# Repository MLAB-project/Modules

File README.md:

# MLAB hardware modules main repository

The MLAB Project was created to develop an universal kit to support hobbyist and professionals in the construction of simple or more complicated devices and instruments (robots, automation systems, testing kits and so on). It is primarily intended for engineers and scientists and it is in continuous development since 2003.

**This repository is archived because its contents have been split into separate repositories in the [MLAB-modules](https://github.com/mlab-modules/) organization. The development of new [MLAB](https://www.mlab.cz) components is still in progress and development has not been suspended. You can read about the reasons of the repository split on the [Discussions thread](https://github.com/orgs/MLAB-project/discussions/1).**

This repository is only a component of the [complete MLAB system](http://www.mlab.cz/)

## Modules

The principle of [Modular LABoratory](http://www.mlab.cz) is based on decomposition of complex systems into smaller cells or bricks (in MLAB called [modules](http://wiki.mlab.cz/doku.php?id=en:moduly)) such as communication interfaces, operational amplifiers, CPU modules, FPGA programmers and many other. Over years of development, [tenths of modules have been created](https://github.com/mlab-modules) - for easier orientation they are sorted into categories which are the first-level folders of this repository. Many modules are included as [repository submodules](https://git-scm.com/book/en/v2/Git-Tools-Submodules) in this parent repository. 

When creating modules, great emphasis is put on the quality of design and construction. The results can, therefore, meet the standards of even the most demanding users from the community of researchers, experimenters and innovators.

## How to start using MLAB

Further information can be found on [MLAB Wiki](http://wiki.mlab.cz/).

There is also a [Mailing list](https://groups.google.com/forum/#!forum/mlab-users) available for users and developers.

## Compatibility

Thanks to careful design, most of the modules are dimensionally and electrically compatible with many other products. Examples include the Arduino platform, the Merkur construction set, optical tables and DIN switchboard systems.

## Applications

See the [list of designs](http://home.mlab.cz/Server/GenIndex/GenIndex.php?path=%2FDesigns&lang=en) for an illustration of the wide spectrum of possible applications.

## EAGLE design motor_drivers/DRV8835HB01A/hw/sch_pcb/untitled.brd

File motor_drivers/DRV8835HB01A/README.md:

[Czech](./README.cs.md)
<!--- module --->
# DRV8835HB01A
<!--- Emodule --->

<!--- subtitle --->2x H-bridge 2V - 11V<!--- Esubtitle --->

<!--- description --->H-bridge-based ICs DRV8835HB. Allows you to control two DC motors in the range voltage 2V to 11V and maximum current of 1.5 A on the engine, or parallel, where it is then possible to control the 3A engine. Or the module can be used to control a stepper motor. <!--- Edescription --->

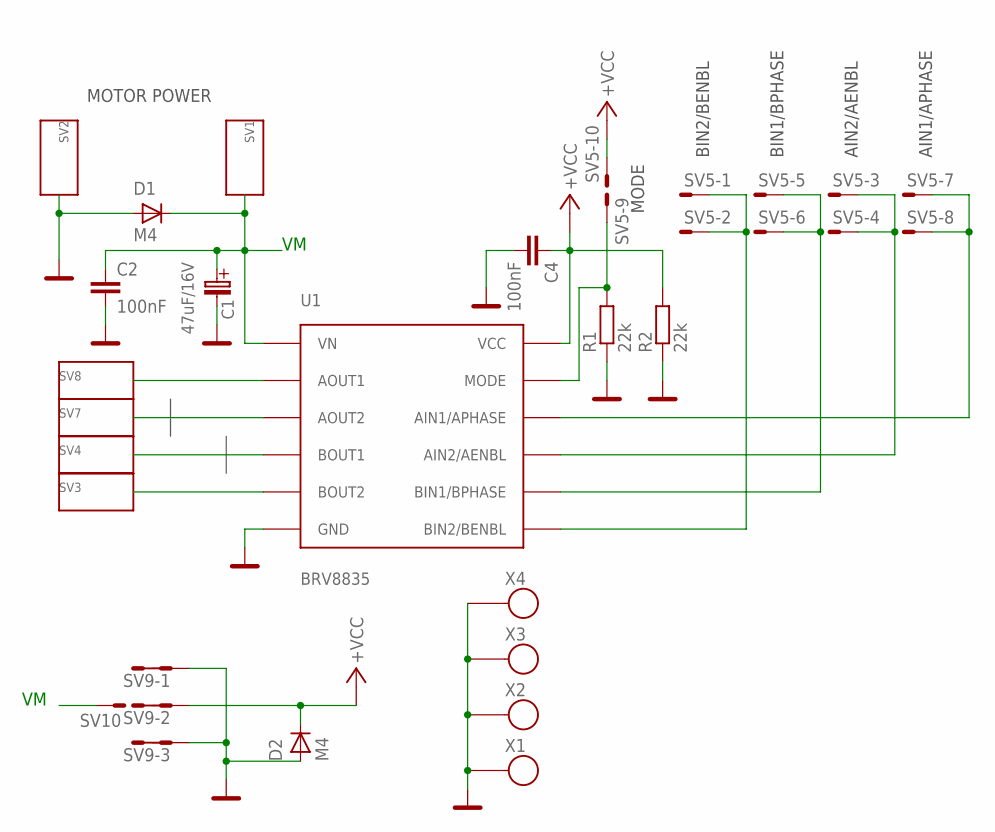
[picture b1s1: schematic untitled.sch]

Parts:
C1: 47uF/16V; C
C2, C4: 100nF; C0805
D1, D2: M4; SMA
R1, R2: 22k; 0805
SV1, SV2, SV3, SV4, SV7, SV8: WAGO256
SV5: MA05-3; MA05-2
SV9: MA03-2
SV10: MA01-1
U1: BRV8835; WSON
X1, X2, X3, X4: SROUB3M

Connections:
+VCC: C4.1, D2.K (C), R2.2, SV5.10, SV9.3, SV9.4, U1.12 (VCC)
GND: C1.- (C_EL-), C2.2, C4.2, D1.A, D2.A, R1.1, R2.1, SV2.1, SV2.A1, SV9.1, SV9.2, SV9.5, SV9.6, U1.6 (GND), U1.P1 (GND), U1.P2 (GND), U1.P3 (GND), U1.P4 (GND), U1.P5 (GND), U1.P6 (GND), U1.P7 (GND), U1.P8 (GND), X1.P$1, X2.P$1, X3.P$1, X4.P$1
unnamed: SV3.1, SV3.A1, U1.5 (BOUT2)
unnamed: SV5.5, SV5.6, U1.8 (BIN1/BPHASE)
unnamed: SV4.1, SV4.A1, U1.4 (BOUT1)
unnamed: SV7.1, SV7.A1, U1.3 (AOUT2)
unnamed: SV8.1, SV8.A1, U1.2 (AOUT1)
unnamed: SV5.1, SV5.2, U1.7 (BIN2/BENBL)
unnamed: R1.2, SV5.9, U1.11 (MODE)
unnamed: SV5.3, SV5.4, U1.9 (AIN2/AENBL)
unnamed: SV5.7, SV5.8, U1.10 (AIN1/APHASE)
VN: C1.+ (C_EL+), C2.1, D1.K (C), SV1.1, SV1.A1, SV10.1, U1.1 (VN)

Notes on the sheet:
AIN1/APHASE
AIN2/AENBL
BIN1/BPHASE
BIN2/BENBL
MODE
MOTOR POWER

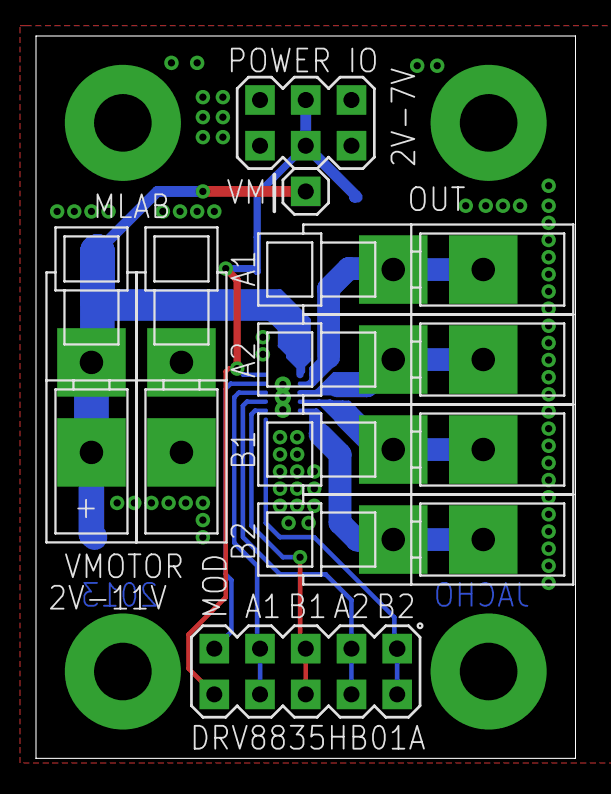
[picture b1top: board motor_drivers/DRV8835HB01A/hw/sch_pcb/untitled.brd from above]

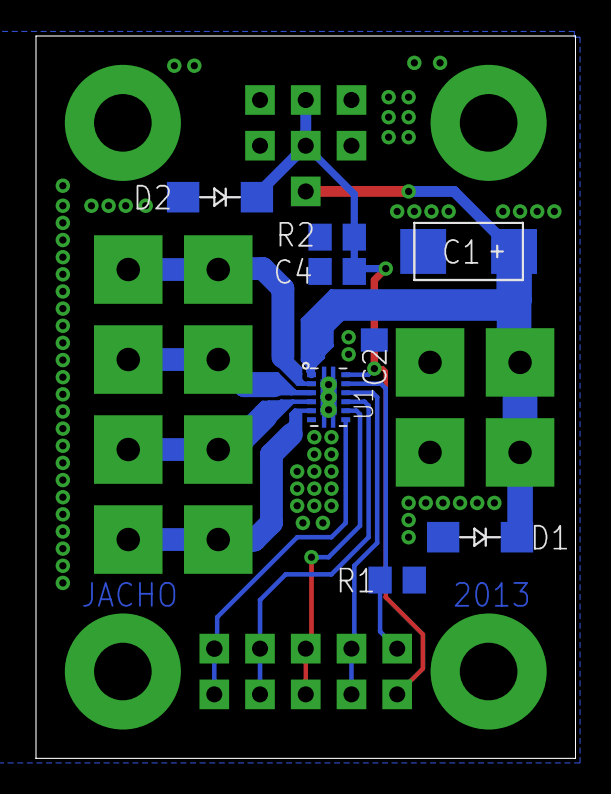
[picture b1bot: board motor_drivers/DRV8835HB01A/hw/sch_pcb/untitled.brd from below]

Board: 2 copper layers, 30.0 x 40.1 mm, 21 parts (8 on the bottom side), 12 nets.

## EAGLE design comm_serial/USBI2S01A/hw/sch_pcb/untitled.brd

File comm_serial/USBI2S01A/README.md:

[Czech](./README.cs.md)
<!--- module --->
# USBI2S01A
<!--- Emodule --->

<!--- subtitle --->USB to I2S bridge<!--- Esubtitle --->

<!--- description --->USB to I2S converter for interfacin I2S audio devices to standard USB port. It is compatible with UAC standard.<!--- Edescription --->

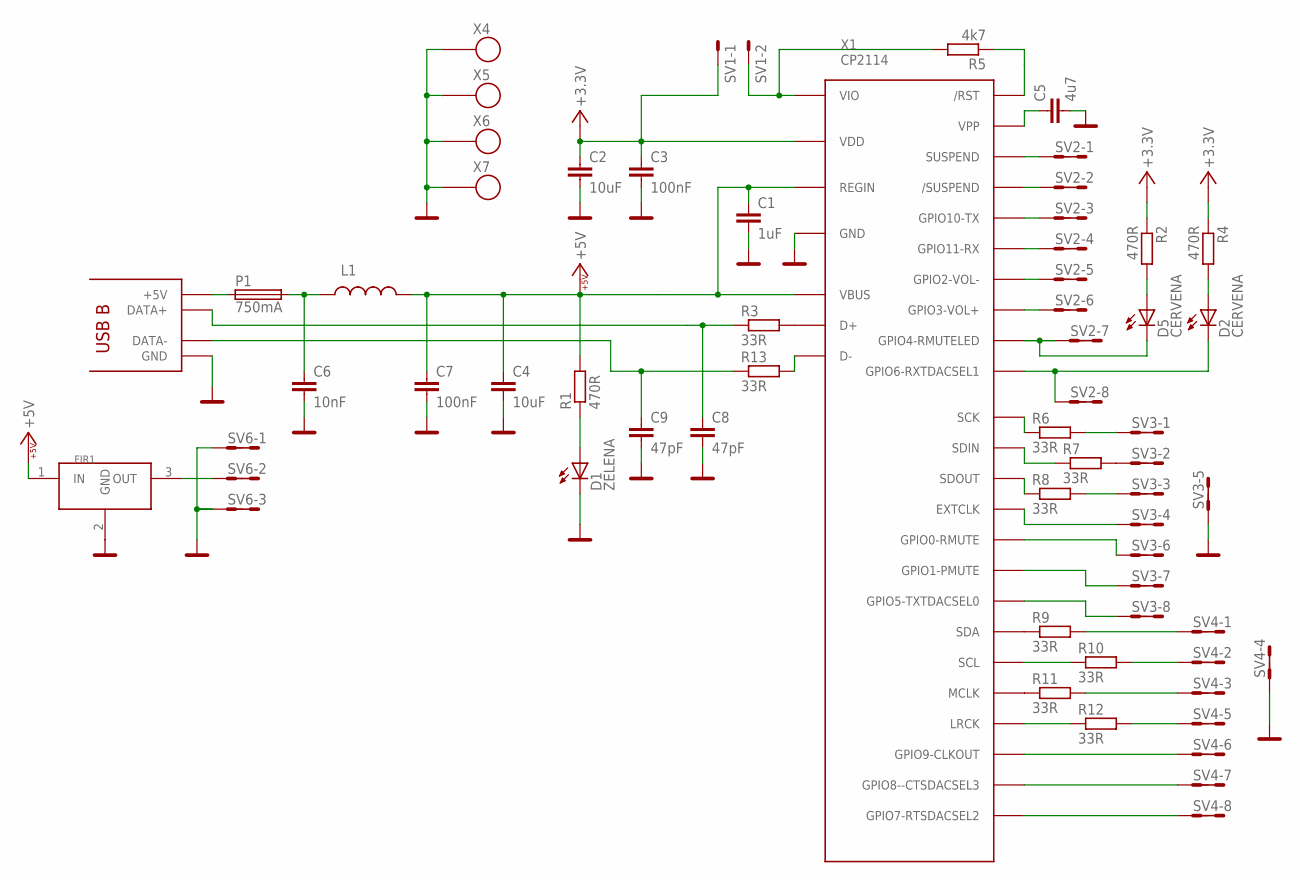
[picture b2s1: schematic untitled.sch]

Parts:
C1: 1uF; C0805
C2, C4: 10uF; C0805
C3, C7: 100nF; C0805
C5: 4u7; C0805
C6: 10nF; C0805
C8, C9: 47pF; C0805
D1: ZELENA; 1206_2
D2, D5: CERVENA; 1206_2
FIR1: FILTR0805; F0805
L1: L0805
P1: 750mA; 1812
R1, R2, R4: 470R; 0805
R3, R6, R7, R8, R9, R10, R11, R12, R13: 33R; 0805
R5: 4k7; 0805
SV1: MA02-1
SV2, SV3, SV4: MA08-2
SV6: MA03-2
X1: CP2114; QFN-32
X3: USB_B
X4, X5, X6, X7: SROUB3M

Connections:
+3.3V: C2.1, C3.1, R2.1, R4.1, SV1.1, X1.7 (VDD)
+5V: C1.1, C4.1, C7.1, FIR1.1 (IN), L1.2, R1.2, X1.8 (REGIN), X1.9 (VBUS)
/SUSPEND: SV2.3, SV2.4, X1.17 (/SUSPEND)
EXTCLK: SV3.7, SV3.8, X1.31 (EXTCLK)
GND: C1.2, C2.2, C3.2, C4.2, C5.2, C6.2, C7.2, C8.2, C9.2, D1.K (C), FIR1.2 (GND), SV3.9, SV3.10, SV4.7, SV4.8, SV6.1, SV6.2, SV6.5, SV6.6, X1.3 (GND), X1.EXP (GND), X3.4 (GND), X3.GND, X3.GND2 (GND), X4.P$1, X5.P$1, X6.P$1, X7.P$1
GP0: SV3.11, SV3.12, X1.30 (GPIO0-RMUTE)
GP1: SV3.13, SV3.14, X1.29 (GPIO1-PMUTE)
GP2: SV2.9, SV2.10, X1.14 (GPIO2-VOL-)
GP3: SV2.11, SV2.12, X1.13 (GPIO3-VOL+)
GP4: D5.K (C), SV2.13, SV2.14, X1.12 (GPIO4-RMUTELED)
GP5: SV3.15, SV3.16, X1.28 (GPIO5-TXTDACSEL0)
GP6: D2.K (C), SV2.15, SV2.16, X1.11 (GPIO6-RXTDACSEL1)
GP7: SV4.15, SV4.16, X1.19 (GPIO7-RTSDACSEL2)
GP08: SV4.13, SV4.14, X1.20 (GPIO8--CTSDACSEL3)
GP9: SV4.11, SV4.12, X1.22 (GPIO9-CLKOUT)
GP10: SV2.5, SV2.6, X1.16 (GPIO10-TX)
GP11: SV2.7, SV2.8, X1.15 (GPIO11-RX)
LRCK: R12.2, SV4.9, SV4.10
MCLK: R11.2, SV4.5, SV4.6
unnamed: C8.1, R3.1, X3.3 (DATA+)
unnamed: C9.1, R13.1, X3.2 (DATA-)
unnamed: FIR1.3 (OUT), SV6.3, SV6.4
unnamed: C5.1, X1.21 (VPP)
unnamed: P1.1, X3.1 (+5V)
unnamed: D1.A, R1.1
unnamed: C6.1, L1.1, P1.2
unnamed: R3.2, X1.4 (D+)
unnamed: R13.2, X1.5 (D-)
unnamed: D5.A, R2.2
unnamed: D2.A, R4.2
unnamed: R5.1, X1.10 (/RST)
unnamed: R8.1, X1.32 (SDOUT)
unnamed: R7.1, X1.1 (SDIN)
unnamed: R6.1, X1.2 (SCK)
unnamed: R9.1, X1.27 (SDA)
unnamed: R10.1, X1.26 (SCL)
unnamed: R11.1, X1.25 (MCLK)
unnamed: R12.1, X1.23 (LRCK)
SCK: R6.2, SV3.1, SV3.2
SCL: R10.2, SV4.3, SV4.4
SDA: R9.2, SV4.1, SV4.2
SDIN: R7.2, SV3.3, SV3.4
SDOUT: R8.2, SV3.5, SV3.6
SUSPEND: SV2.1, SV2.2, X1.18 (SUSPEND)
VIO: R5.2, SV1.2, X1.6 (VIO)

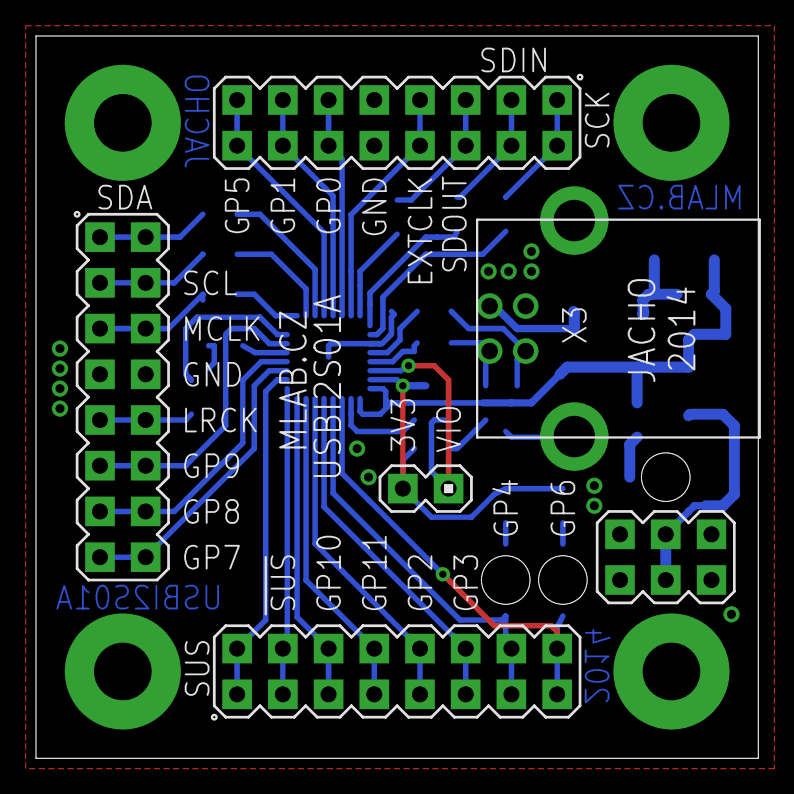
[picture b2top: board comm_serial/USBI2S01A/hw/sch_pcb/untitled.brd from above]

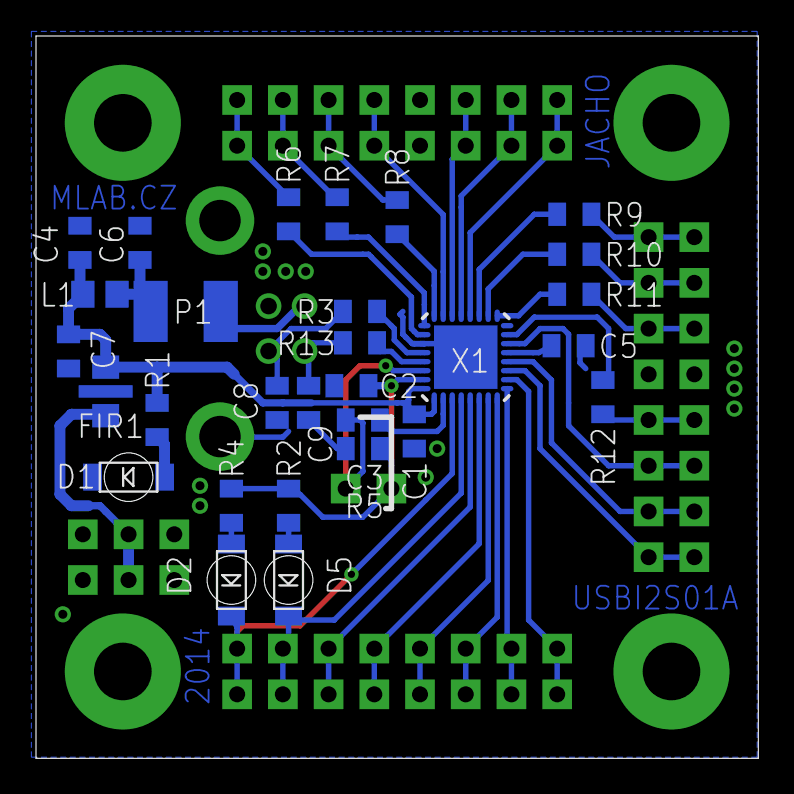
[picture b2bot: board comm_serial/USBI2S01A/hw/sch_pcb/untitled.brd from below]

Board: 2 copper layers, 40.1 x 40.1 mm, 39 parts (29 on the bottom side), 45 nets.

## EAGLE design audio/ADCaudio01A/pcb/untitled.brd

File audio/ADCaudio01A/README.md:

<!--- PrjInfo ---> <!--- Please remove this line after manually editing --->
<!--- 00a56be08b96043df9e37d6aff7b6990 --->
<!--- Created:2022-02-16 22:09:44.047760: ---> 
<!--- Author:: ---> 
<!--- AuthorEmail:: ---> 
<!--- Tags:: ---> 
<!--- Ust:: ---> 
<!--- Label --->
<!--- ELabel ---> 
<!--- Name:ADCaudio01A: --->
# ADCaudio01A
<!--- LongName --->
## Audio to digital converter
<!--- ELongName ---> 

<!--- Lead --->
Replaced module of ADCaudio01B.
<!--- ELead ---> 

<!--- Description --->
<!--- EDescription --->
<!--- Content --->
<!--- EContent --->
<sub><sup> Generated with [MLABweb](https://github.com/MLAB-project/MLABweb). (2022-02-16)</sup></sub>

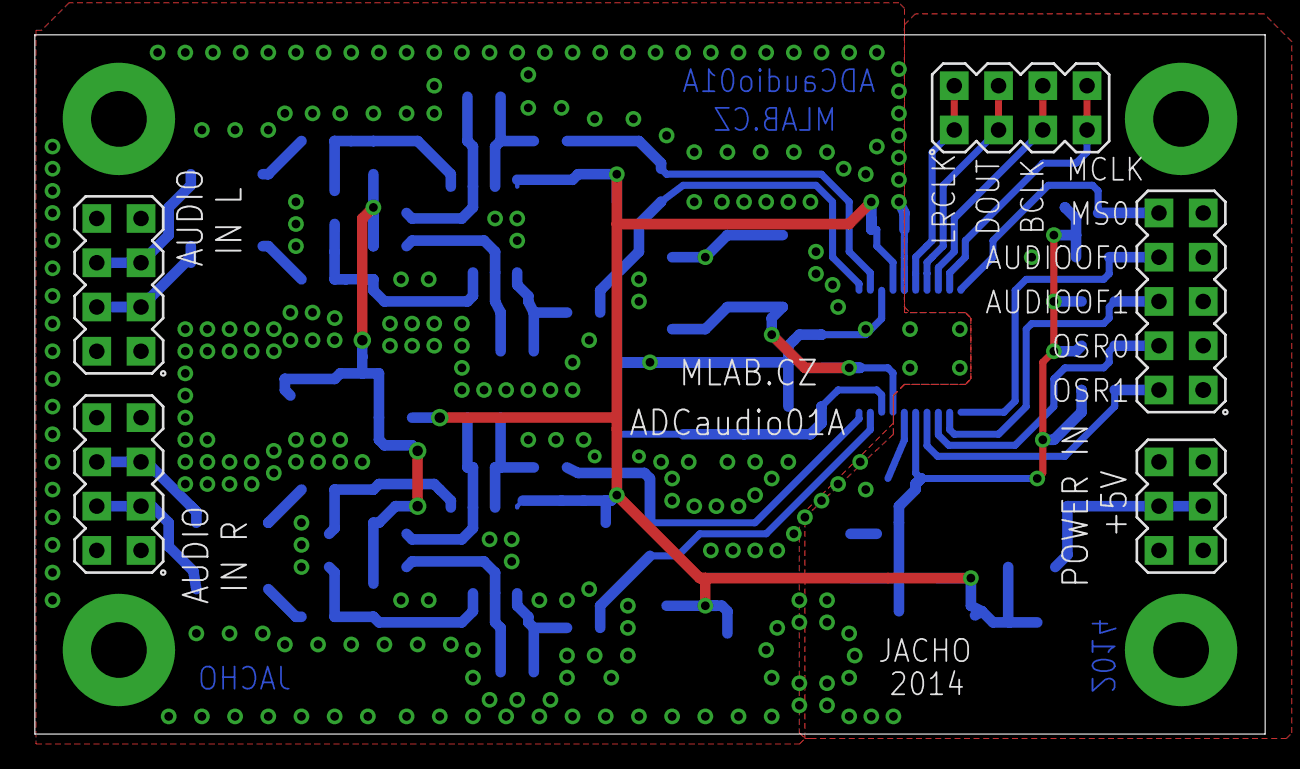
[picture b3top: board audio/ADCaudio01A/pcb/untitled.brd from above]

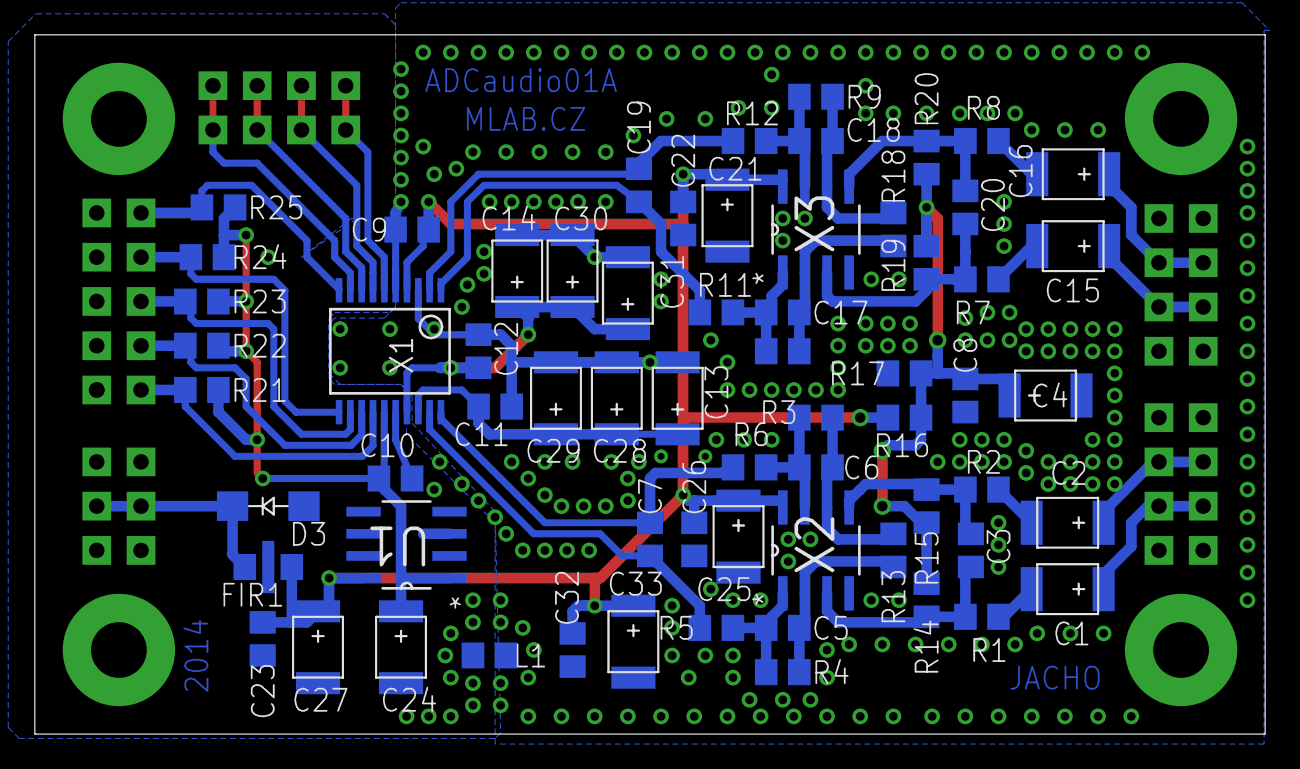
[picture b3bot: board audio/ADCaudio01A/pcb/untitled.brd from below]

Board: 2 copper layers, 70.6 x 40.1 mm, 74 parts (65 on the bottom side), 41 nets.

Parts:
C1, C2, C4, C13, C14, C15, C16, C24, C28, C29, C30, C31: 10uF; B
C3, C7, C19, C20: 4n7; C0805
C5, C6, C17, C18: 180pF; C0805
C8, C11, C12, C22, C23, C26, C32: 100nF; C0805
C9, C10: 4u7; C0805
C21, C25, C27, C33: 47uF; B
D3: M4; SMA
FIR1: F0805
L1: L0805
R1, R2, R3, R4, R7, R8, R9, R10, R13, R14, R15, R16, R17, R18, R19, R20: 1k; 0805
R5, R6, R11, R12, R21, R22, R23, R24, R25: 22R; 0805
SV1: MA05-2
SV2, SV3, SV5: MA04-2
SV4: MA03-2
U1: LE33CD-TR; SOIC127P600X175-8N
X1: WM8786; SSOP20
X2, X3: LT6231CS; SO8
X4, X5, X6, X7: SROUB3M

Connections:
1: C20.1, R7.2, R19.1, X3.3
4: C3.1, R1.2, R14.1, X2.3
+3.3V: C10.2, C24.+, R21.2, R22.2, R23.2, R24.2, R25.2, U1.1, X1.15
+5V: C9.1, C21.+, C22.1, C23.1, C25.+, C26.1, C27.+, C32.1, C33.+, FIR1.3, R16.2, U1.8, X1.4, X2.8, X3.8
AGND: C4.-, C8.2, C9.2, C11.1, C12.1, C13.-, C14.-, C21.-, C22.2, C25.-, C26.2, C28.-, C29.-, C30.-, C31.-, C32.2, C33.-, L1.2, R17.1, SV3.1, SV3.2, SV3.7, SV3.8, SV5.1, SV5.2, SV5.7, SV5.8, X1.3, X1.5, X2.4, X3.4
AUDIOOF0: R24.1, SV1.8, X1.11
AUDIOOF1: R23.1, SV1.6, X1.12
AVDD/2: C4.+, C8.1, R14.2, R15.2, R16.1, R17.2, R19.2, R20.2
BCLK: SV2.5, SV2.6, X1.8
DGND: C10.1, C23.2, C24.-, C27.-, D3.A, FIR1.2, L1.1, SV1.1, SV1.3, SV1.5, SV1.7, SV1.9, SV4.1, SV4.2, SV4.5, SV4.6, U1.2, U1.3, U1.5, U1.6, U1.7, X1.16, X6.P$1, X7.P$1
DOUT: SV2.3, SV2.4, X1.7
LRCLK: SV2.1, SV2.2, X1.6
MCLK: SV2.7, SV2.8, X1.9
MS0: R25.1, SV1.10, X1.10
unnamed: C5.2, R4.1, R13.2, X2.2
unnamed: C1.-, R1.1
unnamed: C16.+, SV5.5, SV5.6
unnamed: C6.2, R3.1, R13.1, X2.6
unnamed: C2.-, R2.1
unnamed: C6.1, R3.2, R6.1, X2.7
unnamed: C7.1, R5.2, X1.19
unnamed: C1.+, SV3.3, SV3.4
unnamed: C17.2, R10.1, R18.2, X3.2
unnamed: C15.-, R7.1
unnamed: C18.2, R9.1, R18.1, X3.6
unnamed: C16.-, R8.1
unnamed: C18.1, R9.2, R12.1, X3.7
unnamed: C19.1, R11.2, X1.1
unnamed: C15.+, SV5.3, SV5.4
unnamed: C20.2, R8.2, R20.1, X3.5
unnamed: C2.+, SV3.5, SV3.6
unnamed: C19.2, R12.2, X1.2
unnamed: C12.2, C14.+, C30.+, C31.+, X1.17
unnamed: C11.2, C13.+, C28.+, C29.+, X1.18
unnamed: C3.2, R2.2, R15.1, X2.5
unnamed: C5.1, R4.2, R5.1, X2.1
unnamed: C17.1, R10.2, R11.1, X3.1
unnamed: C7.2, R6.2, X1.20
unnamed: D3.K, FIR1.1, SV4.3, SV4.4
OSR0: R22.1, SV1.4, X1.13
OSR1: R21.1, SV1.2, X1.14

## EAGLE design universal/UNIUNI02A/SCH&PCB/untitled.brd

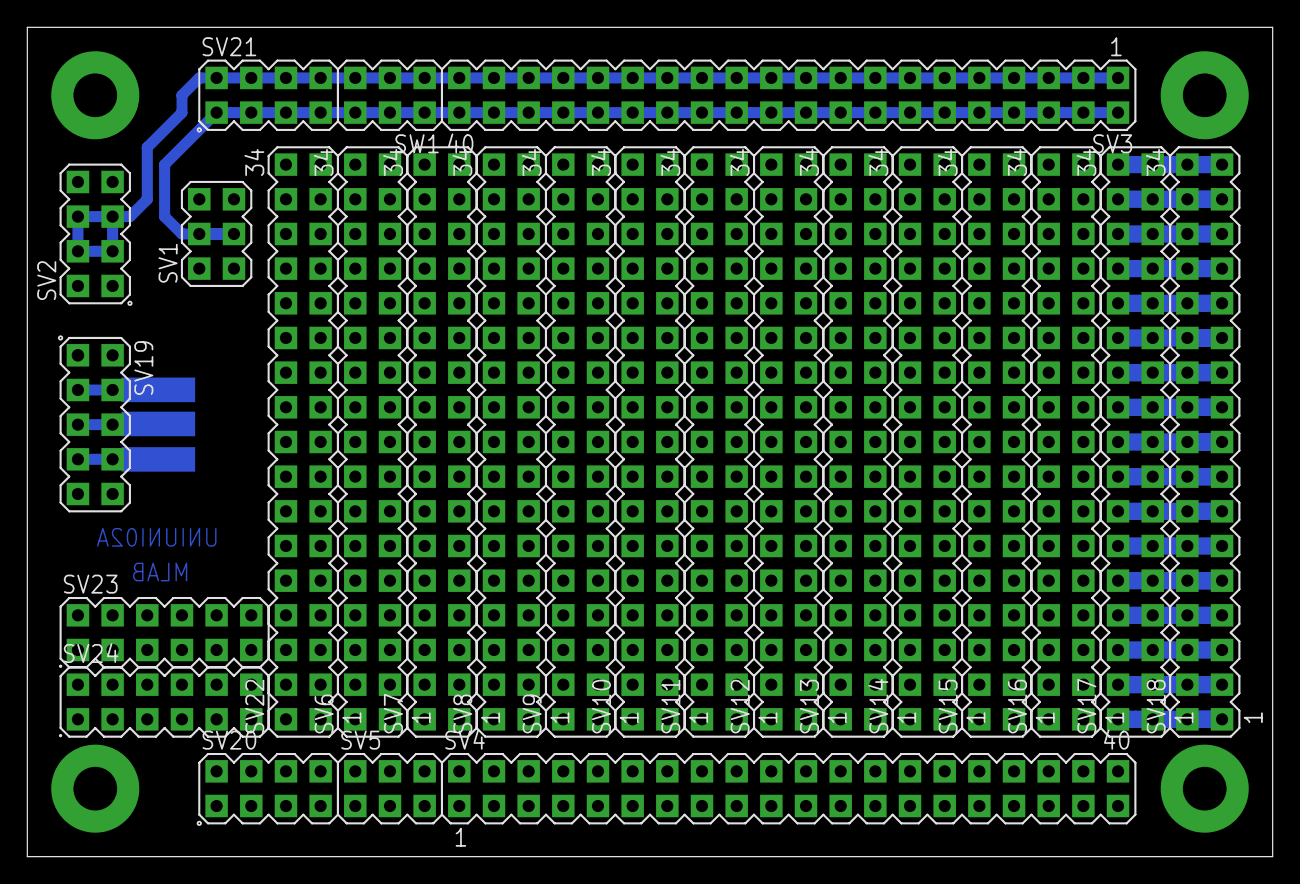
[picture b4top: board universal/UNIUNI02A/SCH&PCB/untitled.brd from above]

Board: 2 copper layers, 91.2 x 60.8 mm, 29 parts (0 on the bottom side), 30 nets.

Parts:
SV1, SV5: MA03-2
SV2, SV20, SV21: MA04-2
SV3, SV4: MA20-2
SV6, SV7, SV8, SV9, SV10, SV11, SV12, SV13, SV14, SV15, SV16, SV17, SV18, SV22: MA17-2
SV19: MA05-2
SV23, SV24: MA06-2
SW1: MA03-2
X3, X4, X5, X6: SROUB3M

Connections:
+5V: SV1.3, SV1.4, SV3.2, SV3.4, SV3.6, SV3.8, SV3.10, SV3.12, SV3.14, SV3.16, SV3.18, SV3.20, SV3.22, SV3.24, SV3.26, SV3.28, SV3.30, SV3.32, SV3.34, SV3.36, SV3.38, SV3.40, SV21.1, SV21.3, SV21.5, SV21.7, SW1.2, SW1.4, SW1.6
+12V: SV2.3, SV2.4, SV2.5, SV2.6, SV3.1, SV3.3, SV3.5, SV3.7, SV3.9, SV3.11, SV3.13, SV3.15, SV3.17, SV3.19, SV3.21, SV3.23, SV3.25, SV3.27, SV3.29, SV3.31, SV3.33, SV3.35, SV3.37, SV3.39, SV21.2, SV21.4, SV21.6, SV21.8, SW1.1, SW1.3, SW1.5
GND: SV1.1, SV1.2, SV1.5, SV1.6, SV2.1, SV2.2, SV2.7, SV2.8, SV4.1, SV4.2, SV4.3, SV4.4, SV4.5, SV4.6, SV4.7, SV4.8, SV4.9, SV4.10, SV4.11, SV4.12, SV4.13, SV4.14, SV4.15, SV4.16, SV4.17, SV4.18, SV4.19, SV4.20, SV4.21, SV4.22, SV4.23, SV4.24, SV4.25, SV4.26, SV4.27, SV4.28, SV4.29, SV4.30, SV4.31, SV4.32, SV4.33, SV4.34, SV4.35, SV4.36, SV4.37, SV4.38, SV4.39, SV4.40, SV5.1, SV5.2, SV5.3, SV5.4, SV5.5, SV5.6, SV19.1, SV19.2, SV19.9, SV19.10, SV20.1, SV20.2, SV20.3, SV20.4, SV20.5, SV20.6, SV20.7, SV20.8, X3.P$1, X4.P$1, X5.P$1, X6.P$1
unnamed: SV19.3, SV19.4
unnamed: SV19.5, SV19.6
unnamed: SV19.7, SV19.8
unnamed: SV17.33, SV17.34, SV18.33, SV18.34
unnamed: SV17.31, SV17.32
unnamed: SV17.29, SV17.30, SV18.29, SV18.30
unnamed: SV17.27, SV17.28, SV18.27, SV18.28
unnamed: SV17.25, SV17.26, SV18.25, SV18.26
unnamed: SV17.23, SV17.24
unnamed: SV17.21, SV17.22, SV18.21, SV18.22
unnamed: SV17.19, SV17.20
unnamed: SV17.17, SV17.18
unnamed: SV17.15, SV17.16
unnamed: SV17.13, SV17.14, SV18.13, SV18.14
unnamed: SV17.11, SV17.12, SV18.11, SV18.12
unnamed: SV17.9, SV17.10
unnamed: SV17.7, SV17.8, SV18.7, SV18.8
unnamed: SV17.5, SV17.6, SV18.5, SV18.6
unnamed: SV17.3, SV17.4, SV18.3, SV18.4
unnamed: SV17.1, SV17.2
unnamed: SV18.31, SV18.32
unnamed: SV18.23, SV18.24
unnamed: SV18.19, SV18.20
unnamed: SV18.17, SV18.18
unnamed: SV18.15, SV18.16
unnamed: SV18.9, SV18.10
unnamed: SV18.1, SV18.2

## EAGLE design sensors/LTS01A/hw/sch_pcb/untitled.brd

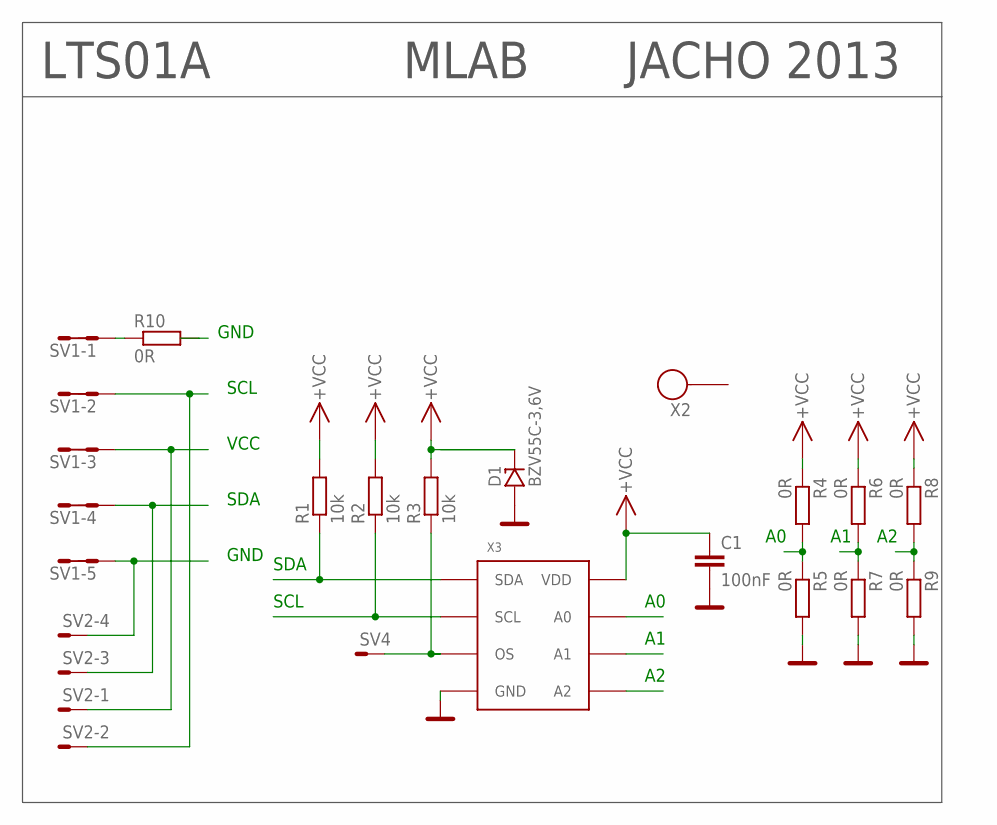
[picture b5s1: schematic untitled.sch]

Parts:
C1: 100nF; C0603
D1: BZV55C-3,6V; MINIMELF
R1, R2, R3: 10k; R0603
R4, R5, R6, R7, R8, R9, R10: 0R; R0603
SV1: MA05-2
SV2: SMD_MA04-01; SMD_MA04-1
SV4: MA01-1
X2: SROUB3M
X3: MAX31725; TDFN8

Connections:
A0: R4.2, R5.1, X3.7 (A0)
A1: R6.2, R7.1, X3.6 (A1)
A2: R8.2, R9.1, X3.5 (A2)
GND: C1.2, D1.A, R5.2, R7.2, R9.2, R10.2, SV1.9, SV1.10, SV2.4, X3.4 (GND), X3.9 (GND)
unnamed: R10.1, SV1.1, SV1.2
OS: R3.1, SV4.1, X3.3 (OS)
SCL: R2.1, SV1.3, SV1.4, SV2.2, X3.2 (SCL)
SDA: R1.1, SV1.7, SV1.8, SV2.3, X3.1 (SDA)
VCC: C1.1, D1.C (K), R1.2, R2.2, R3.2, R4.1, R6.1, R8.1, SV1.5, SV1.6, SV2.1, X3.8 (VDD)

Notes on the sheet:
VCC
GND
SCL
SDA
LTS01A
MLAB
JACHO 2013

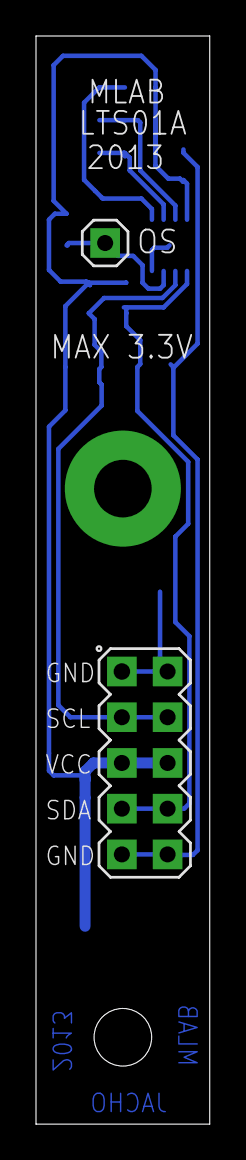
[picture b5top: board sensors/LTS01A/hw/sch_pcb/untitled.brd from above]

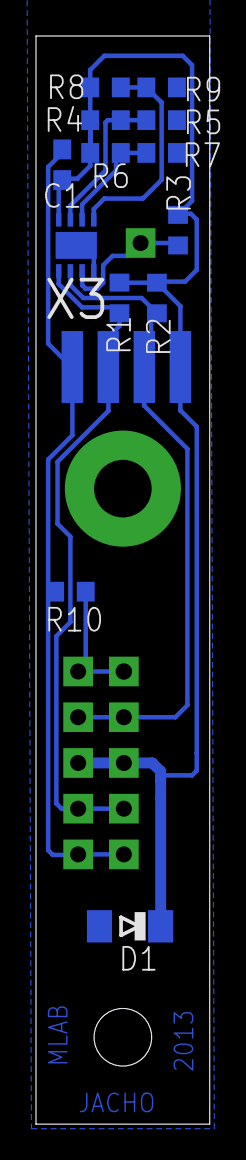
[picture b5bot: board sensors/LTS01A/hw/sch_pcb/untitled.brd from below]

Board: 2 copper layers, 9.7 x 60.5 mm, 17 parts (14 on the bottom side), 9 nets.

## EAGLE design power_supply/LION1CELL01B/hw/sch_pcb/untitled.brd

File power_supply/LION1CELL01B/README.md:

<!--- PrjInfo ---> <!--- Please remove this line after manually editing --->
<!--- 00a56be08b96043df9e37d6aff7b6990 --->
<!--- Created:2022-02-16 21:26:30.300716: ---> 
<!--- Author:: ---> 
<!--- AuthorEmail:: ---> 
<!--- Tags:: ---> 
<!--- Ust:: ---> 
<!--- Label --->
<!--- ELabel ---> 
<!--- Name:LION1CELL01B: --->
# LION1CELL01B
<!--- LongName --->
## Li-ion battery management module
<!--- ELongName ---> 

<!--- Lead --->
Integrated battery management solution for 18650 li-ion batteries. It can measure remaining energy in battery, perform charging cycle from external power source and protect batteries against over voltage or over draining conditions.
<!--- ELead ---> 

<!--- Description --->
<!--- EDescription --->
<!--- Content --->
<!--- EContent --->
<sub><sup> Generated with [MLABweb](https://github.com/MLAB-project/MLABweb). (2022-02-16)</sup></sub>

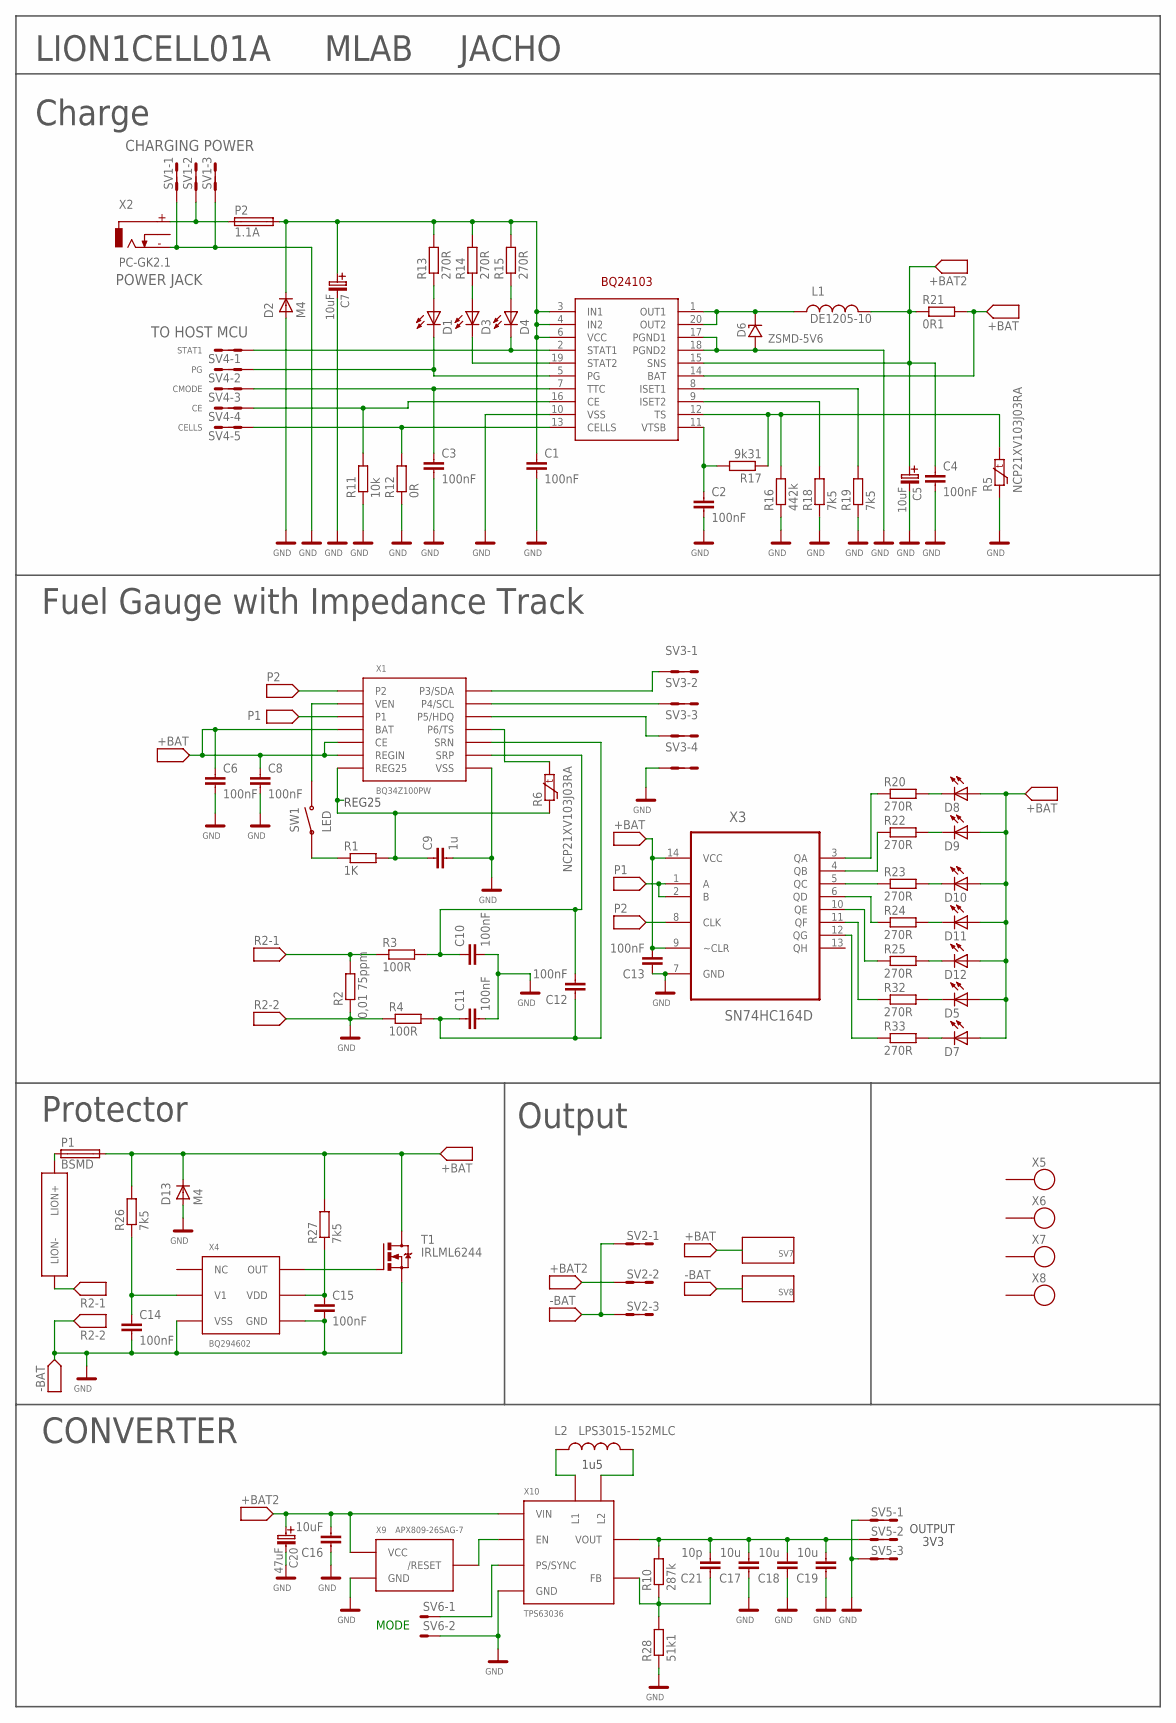
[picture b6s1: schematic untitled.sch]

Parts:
C1, C2, C3, C4, C6, C8, C10, C11, C12, C13, C14, C15: 100nF; C0805
C5, C7: 10uF; B
C9: 1u; C0805
C16: 10uF; C0805
C17, C18, C19: 10u; C0805
C20: 47uF; B
C21: 10p; 0603
D1, D3, D4, D5, D7, D8, D9, D10, D11, D12: LED1206_2; 1206_2
D2: M4; SMB
D6: ZSMD-5V6; MINIMELF
D13: M4; SMA
L1: DE1205-10
L2: LPS3015-152MLC; LPS3015
P1: BSMD; 2410
P2: 1.1A; 1812
R1: 1K; 0805
R2: 0,01 75ppm; 0805
R3, R4: 100R; 0805
R5, R6: NCP21XV103J03RA; 0805
R10: 287k; 0603
R11: 10k; 0805
R12: 0R; 0805
R13, R14, R15, R20, R22, R23, R24, R25, R32, R33: 270R; 0805
R16: 442k; 0805
R17: 9k31; 0805
R18, R19, R26, R27: 7k5; 0805
R21: 0R1; R2512
R28: 51k1; 0603
SV1, SV2, SV5: MA03-2
SV3: MA04-2
SV4: MA05-2
SV6: MA02-1
SV7, SV8: WAGO256
SW1: TACT-64K
T1: IRLML6244; SOT23
U1: BQ24103; RHL_R-VQFN-N20
U$2: LION1
X1: BQ34Z100PW; TSSOP14
X2: DC2.1MM
X3: SN74HC164D; SOIC127P600X175-14N
X4: BQ294602; SON_N6
X5, X6, X7, X8: SROUB3M
X9: APX809-26SAG-7; SOT23
X10: TPS63036; DSBGA8

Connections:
+BAT: C6.1, C8.1, C13.2, D5.A, D7.A, D8.A, D9.A, D10.A, D11.A, D12.A, D13.K (C), P1.2, R21.2, R26.2, R27.2, SV7.1, SV7.A1, T1.3 (D), U1.14 (BAT), X1.4 (BAT), X1.5 (CE), X1.6 (REGIN), X3.9 (~CLR), X3.14 (VCC)
+BAT2: C4.1, C5.+ (C_EL+), C16.2, C20.+ (C_EL+), L1.P$2 (2), R21.1, SV2.3, SV2.4, U1.15 (SNS), X9.3 (VCC), X10.A1 (VIN)
EN: X9.2 (/RESET), X10.A2 (EN)
GND: C1.2, C2.2, C3.2, C4.2, C5.- (C_EL-), C6.2, C7.- (C_EL-), C8.2, C9.2, C10.2, C11.2, C13.1, C14.2, C15.2, C16.1, C17.1, C18.1, C19.1, C20.- (C_EL-), D2.A, D6.A, D13.A, R2.1, R4.1, R5.1, R11.1, R12.1, R16.1, R18.1, R19.1, R28.1, SV1.1, SV1.2, SV1.5, SV1.6, SV2.1, SV2.2, SV2.5, SV2.6, SV3.7, SV3.8, SV5.1, SV5.2, SV5.5, SV5.6, SV6.2, SV8.1, SV8.A1, T1.2 (S), U1.10 (VSS), U1.17 (PGND1), U1.18 (PGND2), X1.8 (VSS), X2.GND (-), X3.7 (GND), X4.3 (VSS), X4.4 (VSS), X4.7 (GND), X9.1 (GND), X10.C2 (GND)
unnamed: C1.1, C7.+ (C_EL+), D2.K (C), P2.2, R13.2, R14.2, R15.2, U1.3 (IN1), U1.4 (IN2), U1.6 (VCC)
unnamed: P1.1, U$2.+ (LION+), U$2.+1 (LION+)
unnamed: D6.C (K), L1.P$1 (1), U1.1 (OUT1), U1.20 (OUT2)
unnamed: D4.K (C), SV4.1, SV4.2, U1.2 (STAT1)
unnamed: D3.K (C), U1.19 (STAT2)
unnamed: D1.K (C), SV4.3, SV4.4, U1.5 (PG)
unnamed: D1.A, R13.1
unnamed: D3.A, R14.1
unnamed: D4.A, R15.1
unnamed: R12.2, SV4.9, SV4.10, U1.13 (CELLS)
unnamed: R11.2, SV4.7, SV4.8, U1.16 (CE)
unnamed: C2.1, R17.2, U1.11 (VTSB)
unnamed: R18.2, U1.9 (ISET2)
unnamed: C3.1, SV4.5, SV4.6, U1.7 (TTC)
unnamed: R19.2, U1.8 (ISET1)
unnamed: SV3.3, SV3.4, X1.13 (P4/SCL)
unnamed: SW1.P$3, SW1.P$4, X1.2 (VEN)
unnamed: R5.2, R16.2, R17.1, U1.12 (TS)
unnamed: L2.1-1 (1), L2.1-2 (1), L2.1-3 (1), X10.B1 (L1)
unnamed: R1.1, SW1.P$1, SW1.P$2
unnamed: SV6.1, X10.B2 (PS/SYNC)
unnamed: R6.2, X1.11 (P6/TS)
unnamed: C10.1, C12.2, R3.2, X1.9 (SRP)
unnamed: SV3.5, SV3.6, X1.12 (P5/HDQ)
unnamed: SV3.1, SV3.2, X1.14 (P3/SDA)
unnamed: L2.2-1 (2), L2.2-2 (2), L2.2-3 (2), X10.C1 (L2)
unnamed: C11.1, C12.1, R4.2, X1.10 (SRN)
unnamed: C17.2, C18.2, C19.2, C21.2, R10.2, SV5.3, SV5.4, X10.D1 (VOUT)
unnamed: C21.1, R10.1, R28.2, X10.D2 (FB)
unnamed: R20.1, X3.3 (QA)
unnamed: D8.K (C), R20.2
unnamed: R22.1, X3.4 (QB)
unnamed: R23.1, X3.5 (QC)
unnamed: R24.1, X3.6 (QD)
unnamed: R25.1, X3.10 (QE)
unnamed: D9.K (C), R22.2
unnamed: D11.K (C), R24.2
unnamed: D12.K (C), R25.2
unnamed: D10.K (C), R23.2
unnamed: C14.1, R26.1, X4.2 (V1)
unnamed: C15.1, R27.1, X4.5 (VDD)
unnamed: T1.1 (G), X4.6 (OUT)
unnamed: R32.1, X3.11 (QF)
unnamed: R33.1, X3.12 (QG)
unnamed: D5.K (C), R32.2
unnamed: D7.K (C), R33.2
unnamed: P2.1, SV1.3, SV1.4, X2.+
P1: X1.3 (P1), X3.1 (A), X3.2 (B)
P2: X1.1 (P2), X3.8 (CLK)
R2: R2.2, R3.1, U$2.- (LION-), U$2.-1 (LION-)
REG25: C9.1, R1.2, R6.1, X1.7 (REG25)

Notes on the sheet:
STAT1
CMODE
CELLS
POWER JACK
TO HOST MCU
CHARGING POWER
LED
Protector
Fuel Gauge with Impedance Track
Charge
Output
LION1CELL01A
MLAB
JACHO
REG25
1u5
3V3
OUTPUT
MODE
CONVERTER

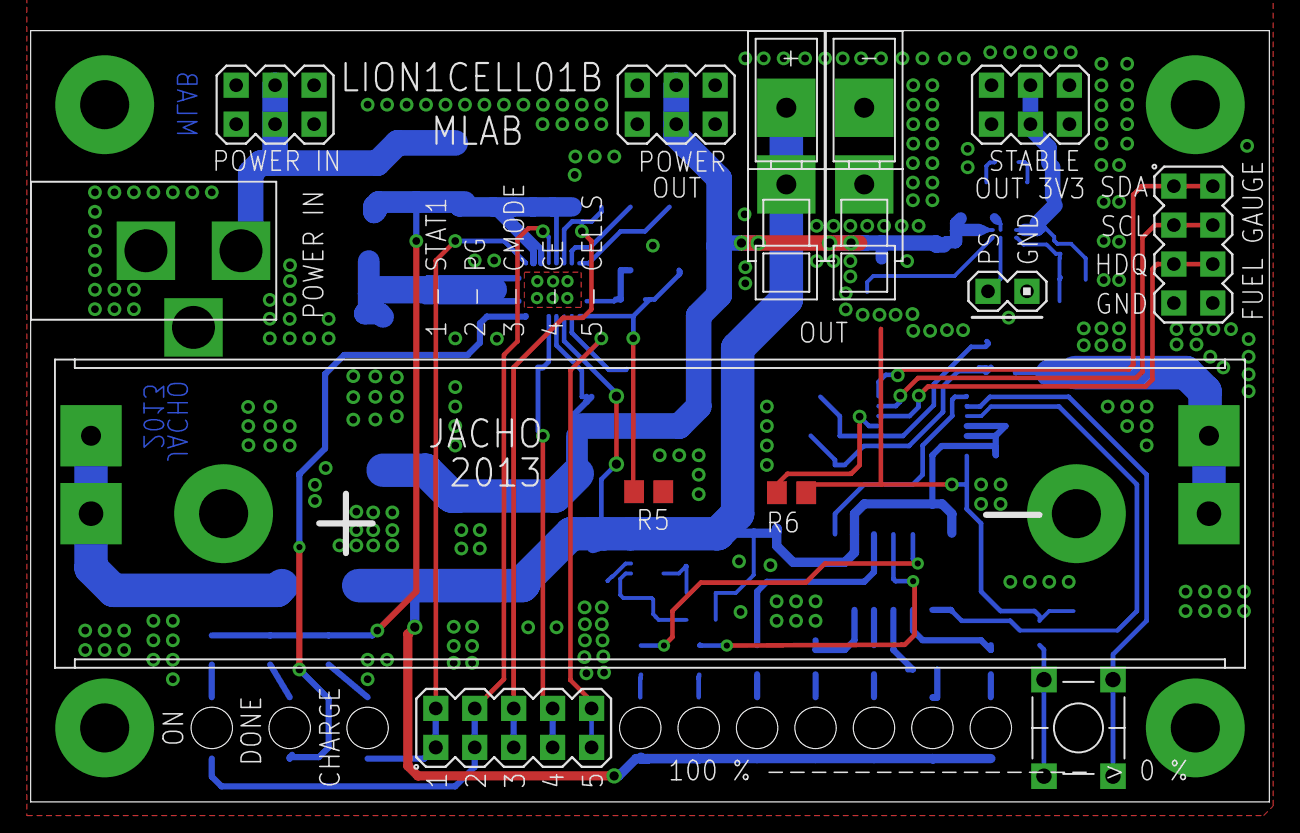
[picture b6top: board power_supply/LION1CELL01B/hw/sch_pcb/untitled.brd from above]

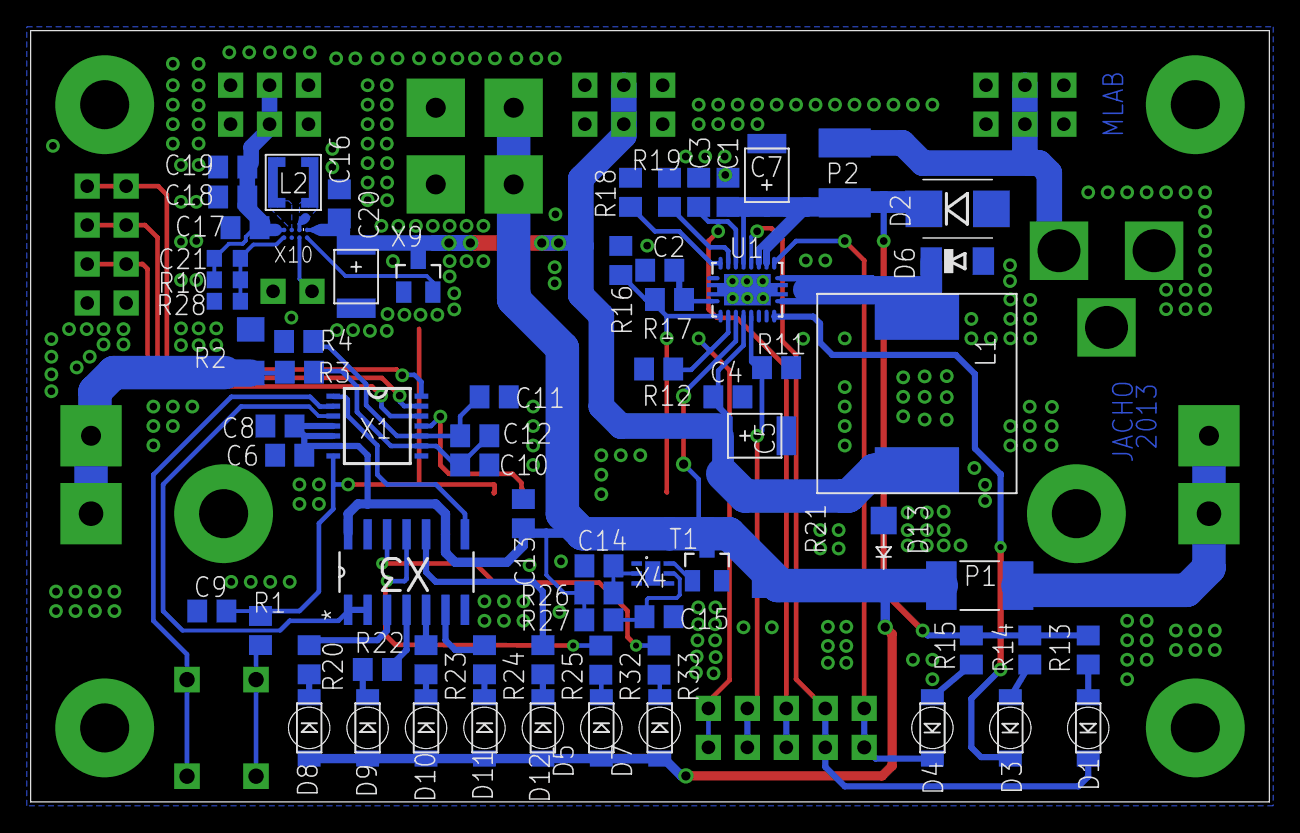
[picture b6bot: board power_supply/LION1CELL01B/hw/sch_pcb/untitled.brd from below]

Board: 2 copper layers, 80.8 x 50.3 mm, 87 parts (70 on the bottom side), 55 nets.

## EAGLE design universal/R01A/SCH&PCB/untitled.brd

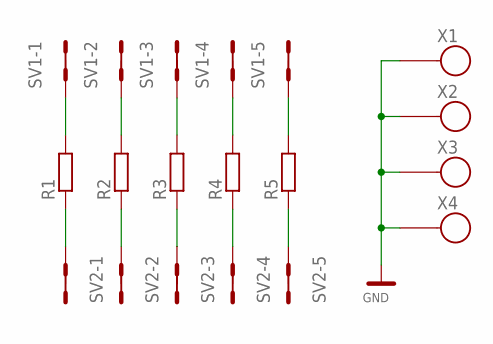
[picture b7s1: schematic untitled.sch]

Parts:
R1, R2, R3, R4, R5: R0805; 0805
SV1, SV2: MA05-2
X1, X2, X3, X4: SROUB3M

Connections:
GND: X1.P$1, X2.P$1, X3.P$1, X4.P$1
unnamed: R1.1, SV2.1, SV2.2
unnamed: R2.1, SV2.3, SV2.4
unnamed: R3.1, SV2.5, SV2.6
unnamed: R4.1, SV2.7, SV2.8
unnamed: R1.2, SV1.1, SV1.2
unnamed: R2.2, SV1.3, SV1.4
unnamed: R3.2, SV1.5, SV1.6
unnamed: R4.2, SV1.7, SV1.8
unnamed: R5.1, SV2.9, SV2.10
unnamed: R5.2, SV1.9, SV1.10

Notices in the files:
parts and their libraries:
PaJa_22: Copyright (C) PaJa 2001-2010
